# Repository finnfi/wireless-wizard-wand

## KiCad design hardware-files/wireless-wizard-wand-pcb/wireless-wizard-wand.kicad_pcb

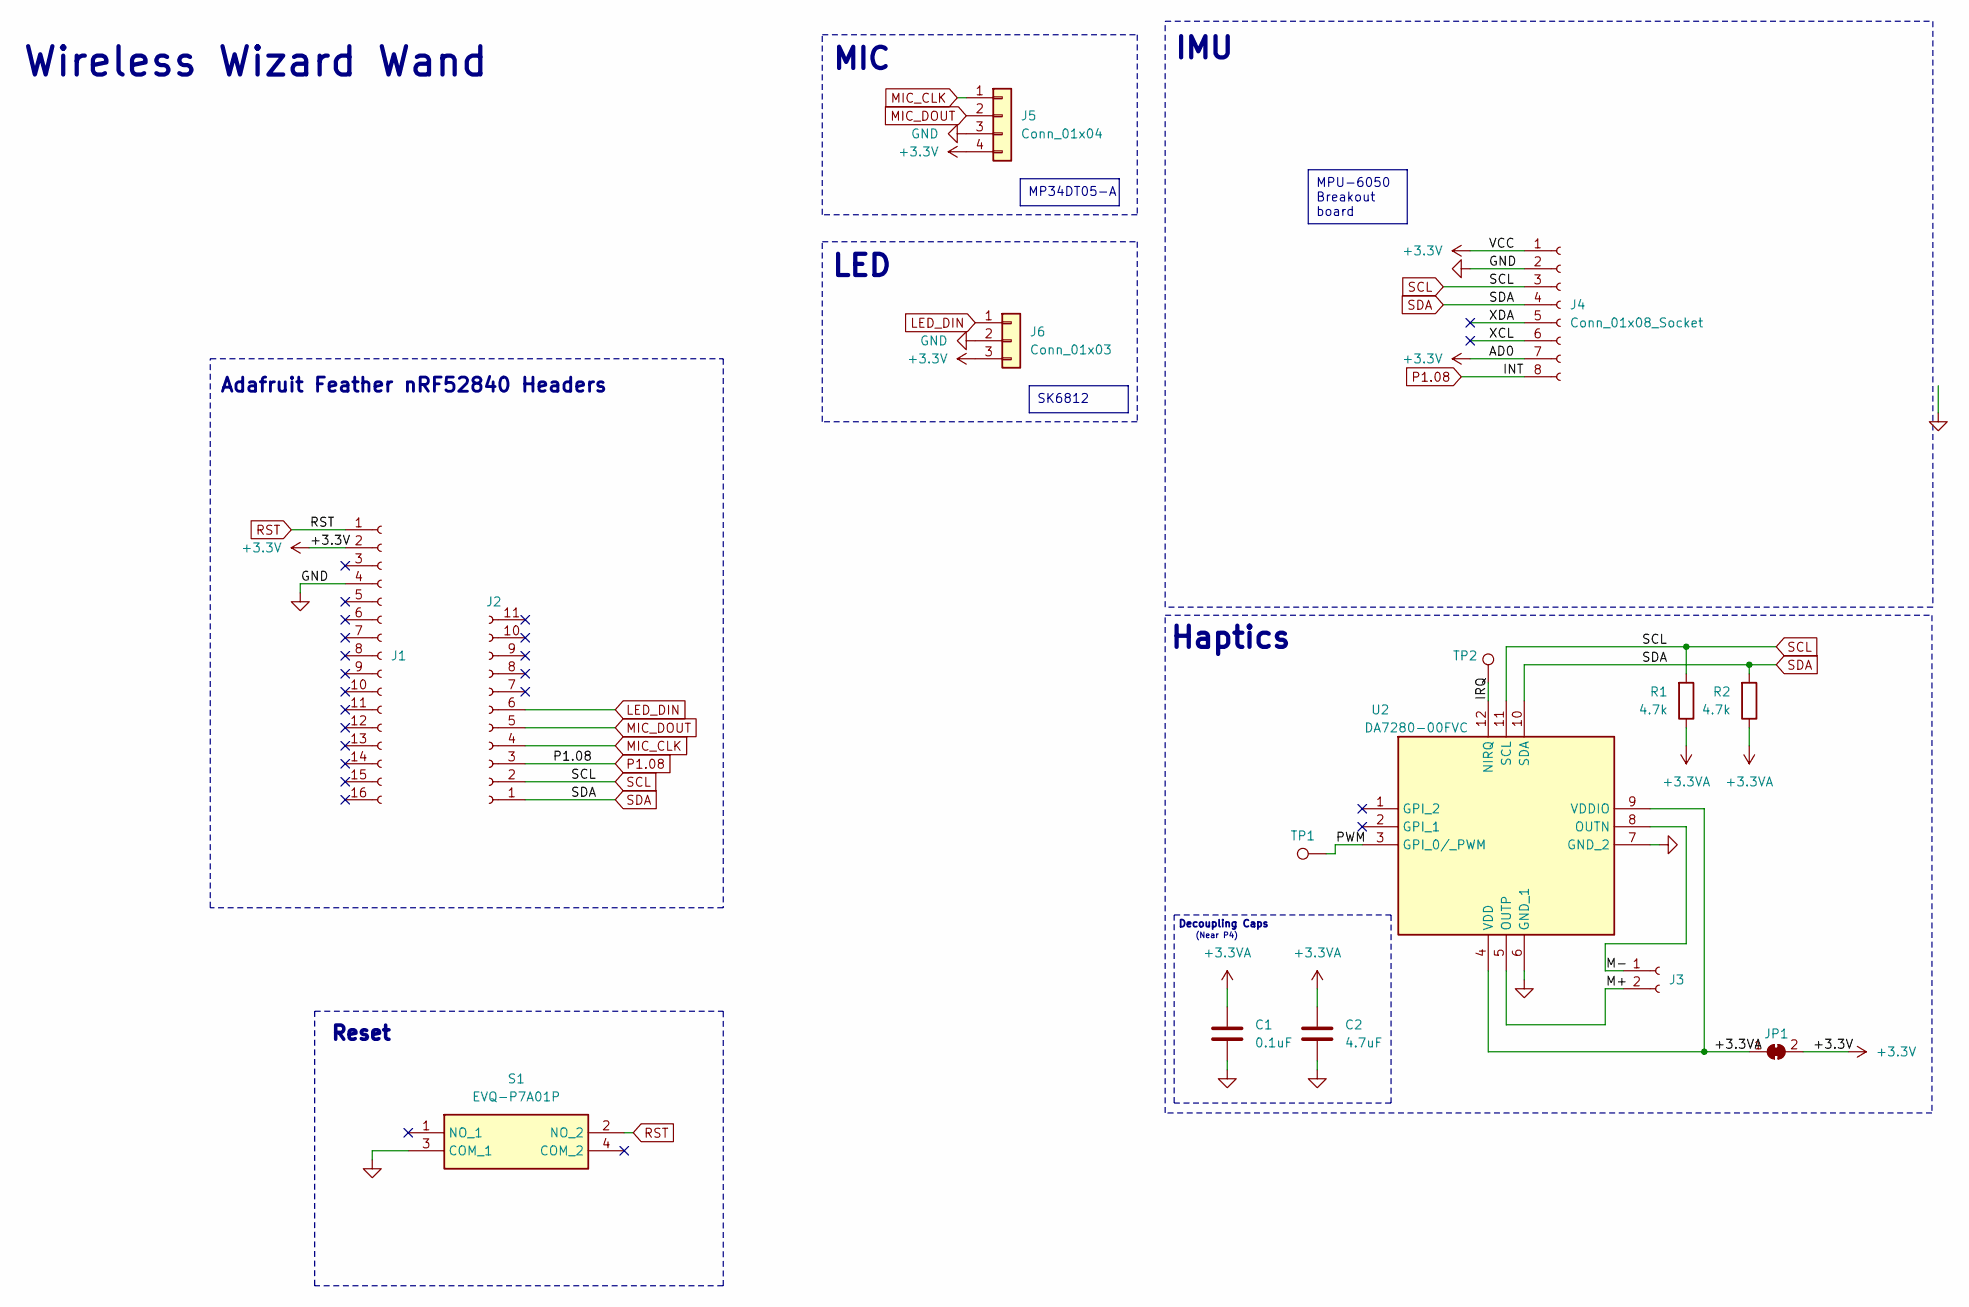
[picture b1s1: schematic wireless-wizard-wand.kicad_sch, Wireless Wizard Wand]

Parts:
C1: 0.1uF; C_0805_2012Metric
C2: 4.7uF; C_0805_2012Metric
J1: Conn_01x16_Socket; PinSocket_1x16_P2.54mm_Vertical
J2: Conn_01x11_Socket; PinSocket_1x11_P2.54mm_Vertical
J3: Conn_01x02_Socket; PinSocket_1x02_P2.54mm_Vertical
J4: Conn_01x08_Socket; PinSocket_1x08_P2.54mm_Vertical
J5: Conn_01x04; PinHeader_1x04_P2.54mm_Vertical
J6: Conn_01x03; PinHeader_1x03_P2.54mm_Vertical
JP1: SolderJumper_2_Bridged; SolderJumper-2_P1.3mm_Bridged_RoundedPad1.0x1.5mm
R1, R2: 4.7k; R_0805_2012Metric
S1: EVQ-P7A01P; EVQP7J01P; Manufacturer_Part_Number EVQ-P7A01P; Mouser Part Number 667-EVQP7A01P
TP1, TP2: TestPoint; TestPoint_Pad_D1.5mm
U2: DA7280-00FVC; QFN65P300X300X84-12N; Manufacturer_Part_Number DA7280-00FVC; Mouser Part Number 724-DA7280-00FVC

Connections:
+3.3V: J1.2, J4.1, J4.7, J5.4, J6.3, JP1.2 (B)
+3.3VA: C1.1, C2.1, JP1.1 (A), R1.1, R2.1, U2.4 (VDD), U2.9 (VDDIO)
/IRQ: TP2.1, U2.12 (NIRQ)
/M+: J3.2, U2.5 (OUTP)
/M-: J3.1, U2.8 (OUTN)
/PWM: TP1.1, U2.3 (GPI_0/_PWM)
/XCL: J4.6
/XDA: J4.5
GND: C1.2, C2.2, J1.4, J4.2, J5.3, J6.2, S1.3 (COM_1), U2.6 (GND_1), U2.7 (GND_2)
LED_DIN: J2.6, J6.1
MIC_CLK: J2.4, J5.1
MIC_DOUT: J2.5, J5.2
P1.08: J2.3, J4.8
RST: J1.1, S1.2 (NO_2)
SCL: J2.2, J4.3, R1.2, U2.11 (SCL)
SDA: J2.1, J4.4, R2.2, U2.10 (SDA)

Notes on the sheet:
SK6812
MP34DT05-A
MPU-6050 Breakout board
IMU
Decoupling Caps
Reset
LED
Wireless Wizard Wand
Adafruit Feather nRF52840 Headers
MIC
(Near P4)
Haptics

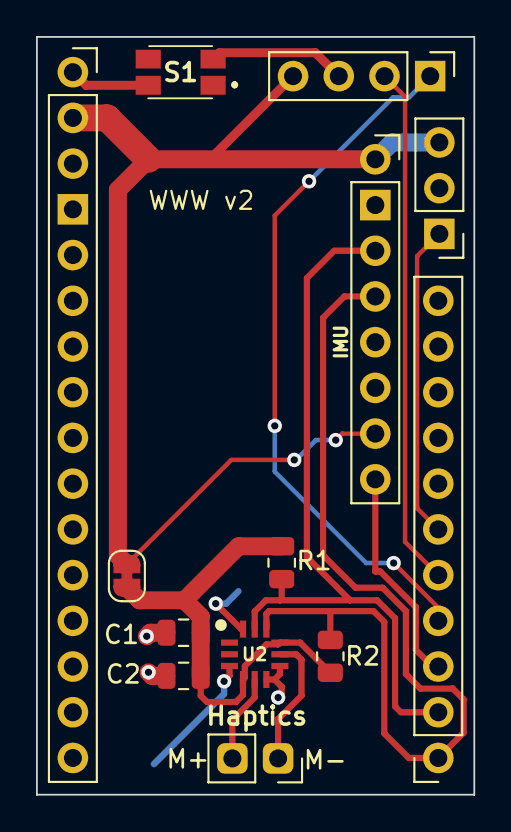
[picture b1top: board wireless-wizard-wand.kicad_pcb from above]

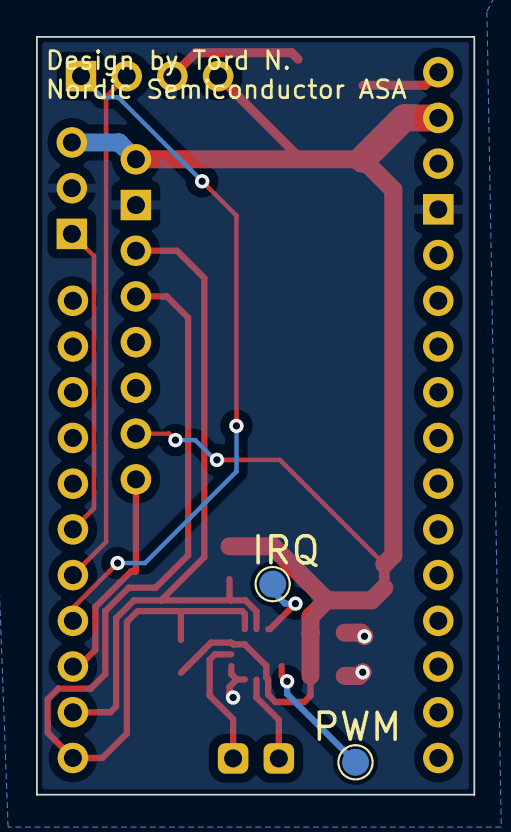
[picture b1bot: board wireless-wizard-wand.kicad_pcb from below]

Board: 2 copper layers, 24.3 x 42.1 mm, 15 parts (2 on the bottom side), 14 nets.

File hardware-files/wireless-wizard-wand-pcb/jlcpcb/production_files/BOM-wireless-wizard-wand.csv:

Comment,Designator,Footprint,LCSC
Conn_01x04,J5,PinHeader_1x04_P2.54mm_Vertical,
4.7k,R1,R_0805_2012Metric,
Conn_01x11_Socket,J2,PinSocket_1x11_P2.54mm_Vertical,
Conn_01x08_Socket,J4,PinSocket_1x08_P2.54mm_Vertical,
0.1uF,C1,C_0805_2012Metric,
4.7uF,C2,C_0805_2012Metric,
Conn_01x03,J6,PinHeader_1x03_P2.54mm_Vertical,
EVQ-P7A01P,S1,EVQP7J01P,
Conn_01x16_Socket,J1,PinSocket_1x16_P2.54mm_Vertical,
Conn_01x02_Socket,J3,PinSocket_1x02_P2.54mm_Vertical,
DA7280-00FVC,U2,QFN65P300X300X84-12N,
4.7k,R2,R_0805_2012Metric,
TestPoint,TP1,TestPoint_Pad_D1.5mm,
TestPoint,TP2,TestPoint_Pad_D1.5mm,

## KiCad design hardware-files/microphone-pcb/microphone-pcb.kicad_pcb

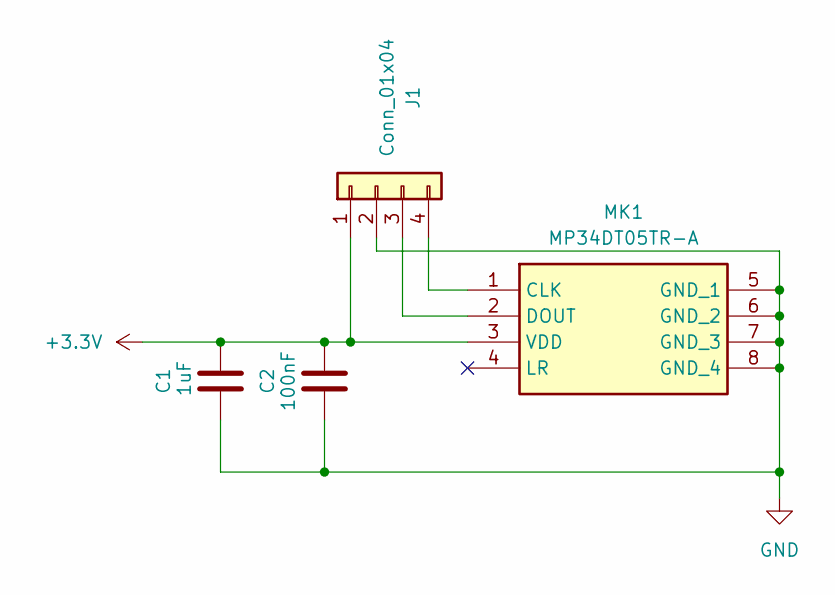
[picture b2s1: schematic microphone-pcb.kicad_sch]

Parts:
C1: 1uF; C_0805_2012Metric_Pad1.18x1.45mm_HandSolder
C2: 100nF; C_0805_2012Metric_Pad1.18x1.45mm_HandSolder
J1: Conn_01x04; PinHeader_1x04_P2.54mm_Horizontal
MK1: MP34DT05TR-A; MP34DT05TRA; Mouser Part Number 511-MP34DT05TR-A

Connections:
+3.3V: C1.2, C2.1, J1.1, MK1.3 (VDD)
GND: C1.1, C2.2, J1.2, MK1.5 (GND_1), MK1.6 (GND_2), MK1.7 (GND_3), MK1.8 (GND_4)
unnamed: J1.3, MK1.2 (DOUT)
unnamed: J1.4, MK1.1 (CLK)

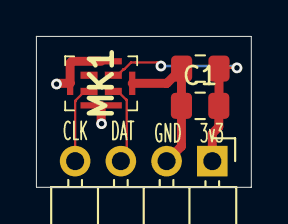
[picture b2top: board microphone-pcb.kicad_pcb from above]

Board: 2 copper layers, 11.9 x 8.4 mm, 4 parts (0 on the bottom side), 4 nets.

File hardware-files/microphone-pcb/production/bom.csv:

Designator,Footprint,Quantity,Value,LCSC Part #
C1,0402,1,1uF,
C2,0402,1,100nF,
J1,PinHeader_1x04_P2.54mm_Horizontal,1,Conn_01x04,
MK1,MP34DT05TRA,1,MP34DT05TR-A,

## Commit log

2025-01-18 recorded test-data
